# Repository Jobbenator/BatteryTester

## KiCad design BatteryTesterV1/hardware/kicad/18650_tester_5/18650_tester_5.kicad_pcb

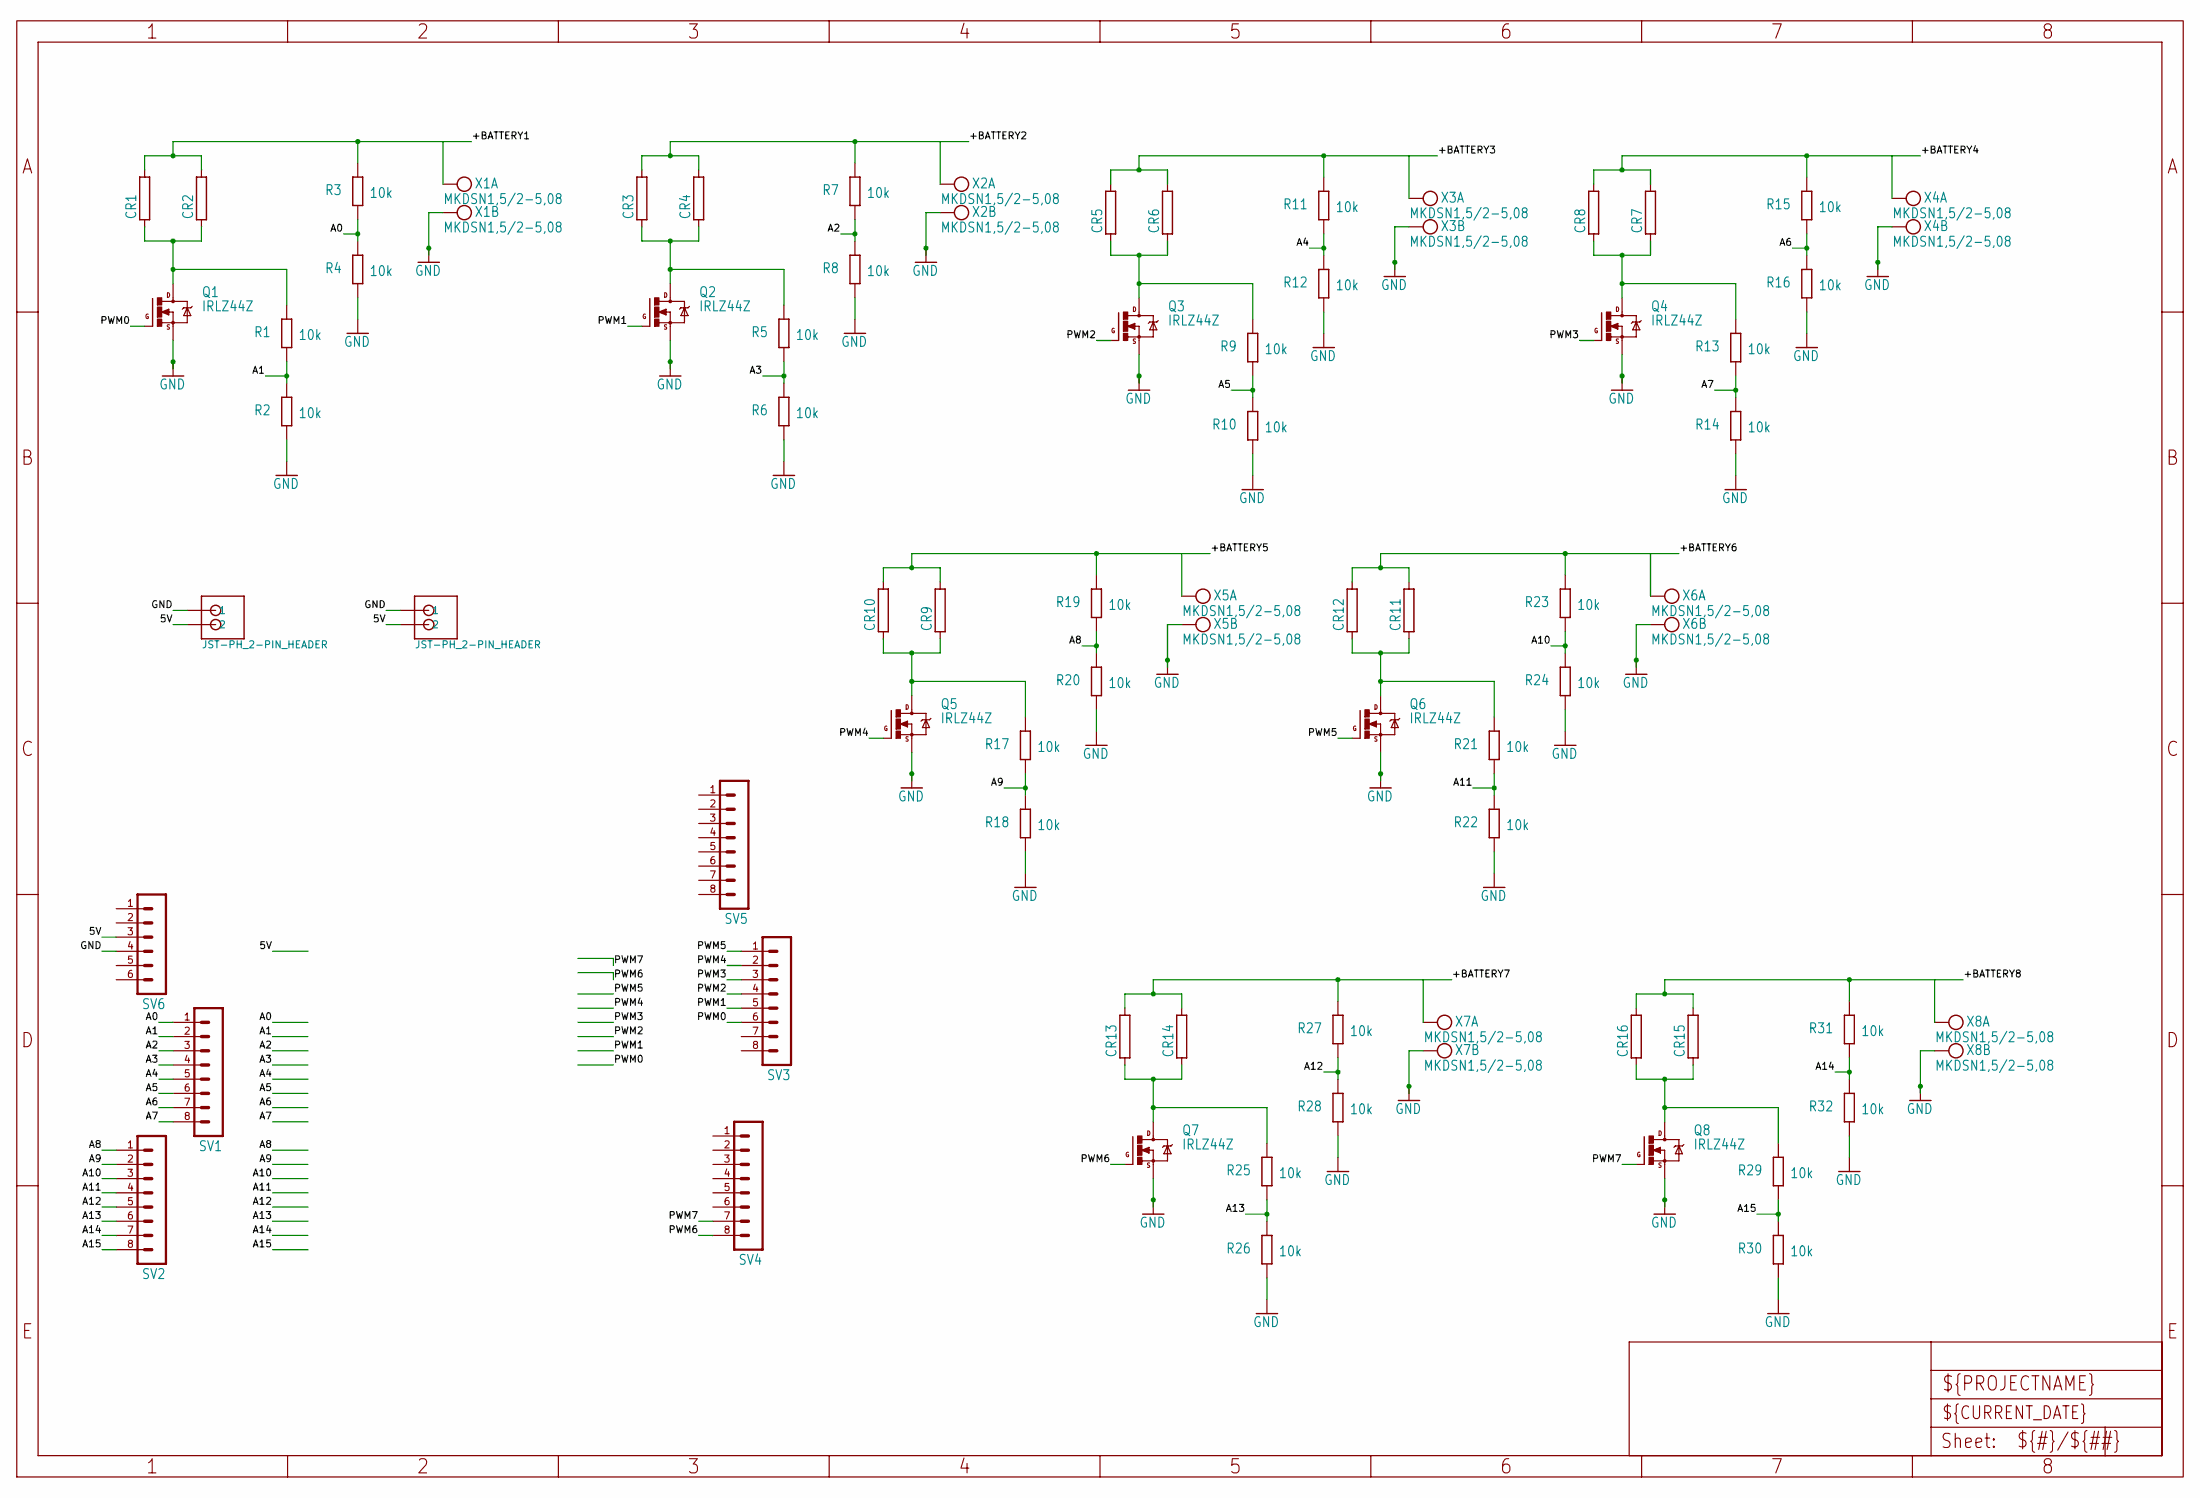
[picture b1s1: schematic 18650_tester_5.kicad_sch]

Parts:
CR1, CR2, CR3, CR4, CR5, CR6, CR7, CR8, CR9, CR10, CR11, CR12, CR13, CR14, CR15, CR16: RRWM6X22; RWM6X22
Q1, Q2, Q3, Q4, Q5, Q6, Q7, Q8: IRLZ44Z; TO220BH
R1, R2, R3, R4, R5, R6, R7, R8, R9, R10, R11, R12, R13, R14, R15, R16, R17, R18, R19, R20, R21, R22, R23, R24, R25, R26, R27, R28, R29, R30, R31, R32: 10k; M1206
SV1, SV2, SV3, SV4, SV5: MA08-1
SV6: MA06-1
U$2, U$3: JST-PH_2-PIN_HEADER; JST_B2B-PH_HEADER
X1, X2, X3, X4, X5, X6, X7, X8: MKDSN1,5/2-5,08; MKDSN1,5_2-5,08

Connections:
5V: SV6.3, U$2.P2 (2), U$3.P2 (2)
+BATTERY1: CR1.2, CR2.2, R3.2, X1.1
+BATTERY2: CR3.2, CR4.2, R7.2, X2.1
+BATTERY3: CR5.2, CR6.2, R11.2, X3.1
+BATTERY4: CR7.2, CR8.2, R15.2, X4.1
+BATTERY5: CR9.2, CR10.2, R19.2, X5.1
+BATTERY6: CR11.2, CR12.2, R23.2, X6.1
+BATTERY7: CR13.2, CR14.2, R27.2, X7.1
+BATTERY8: CR15.2, CR16.2, R31.2, X8.1
A0: R3.1, R4.2, SV1.1
A1: R1.1, R2.2, SV1.2
A2: R7.1, R8.2, SV1.3
A3: R5.1, R6.2, SV1.4
A4: R11.1, R12.2, SV1.5
A5: R9.1, R10.2, SV1.6
A6: R15.1, R16.2, SV1.7
A7: R13.1, R14.2, SV1.8
A8: R19.1, R20.2, SV2.1
A9: R17.1, R18.2, SV2.2
A10: R23.1, R24.2, SV2.3
A11: R21.1, R22.2, SV2.4
A12: R27.1, R28.2, SV2.5
A13: R25.1, R26.2, SV2.6
A14: R31.1, R32.2, SV2.7
A15: R29.1, R30.2, SV2.8
GND: Q1.S, Q2.S, Q3.S, Q4.S, Q5.S, Q6.S, Q7.S, Q8.S, R2.1, R4.1, R6.1, R8.1, R10.1, R12.1, R14.1, R16.1, R18.1, R20.1, R22.1, R24.1, R26.1, R28.1, R30.1, R32.1, SV6.4, U$2.P1 (1), U$3.P1 (1), X1.2, X2.2, X3.2, X4.2, X5.2, X6.2, X7.2, X8.2
unnamed: CR3.1, CR4.1, Q2.D, R5.2
unnamed: CR5.1, CR6.1, Q3.D, R9.2
unnamed: CR1.1, CR2.1, Q1.D, R1.2
unnamed: CR7.1, CR8.1, Q4.D, R13.2
unnamed: CR9.1, CR10.1, Q5.D, R17.2
unnamed: CR11.1, CR12.1, Q6.D, R21.2
unnamed: CR13.1, CR14.1, Q7.D, R25.2
unnamed: CR15.1, CR16.1, Q8.D, R29.2
PWM0: Q1.G, SV3.6
PWM1: Q2.G, SV3.5
PWM2: Q3.G, SV3.4
PWM3: Q4.G, SV3.3
PWM4: Q5.G, SV3.2
PWM5: Q6.G, SV3.1
PWM6: Q7.G, SV4.8
PWM7: Q8.G, SV4.7

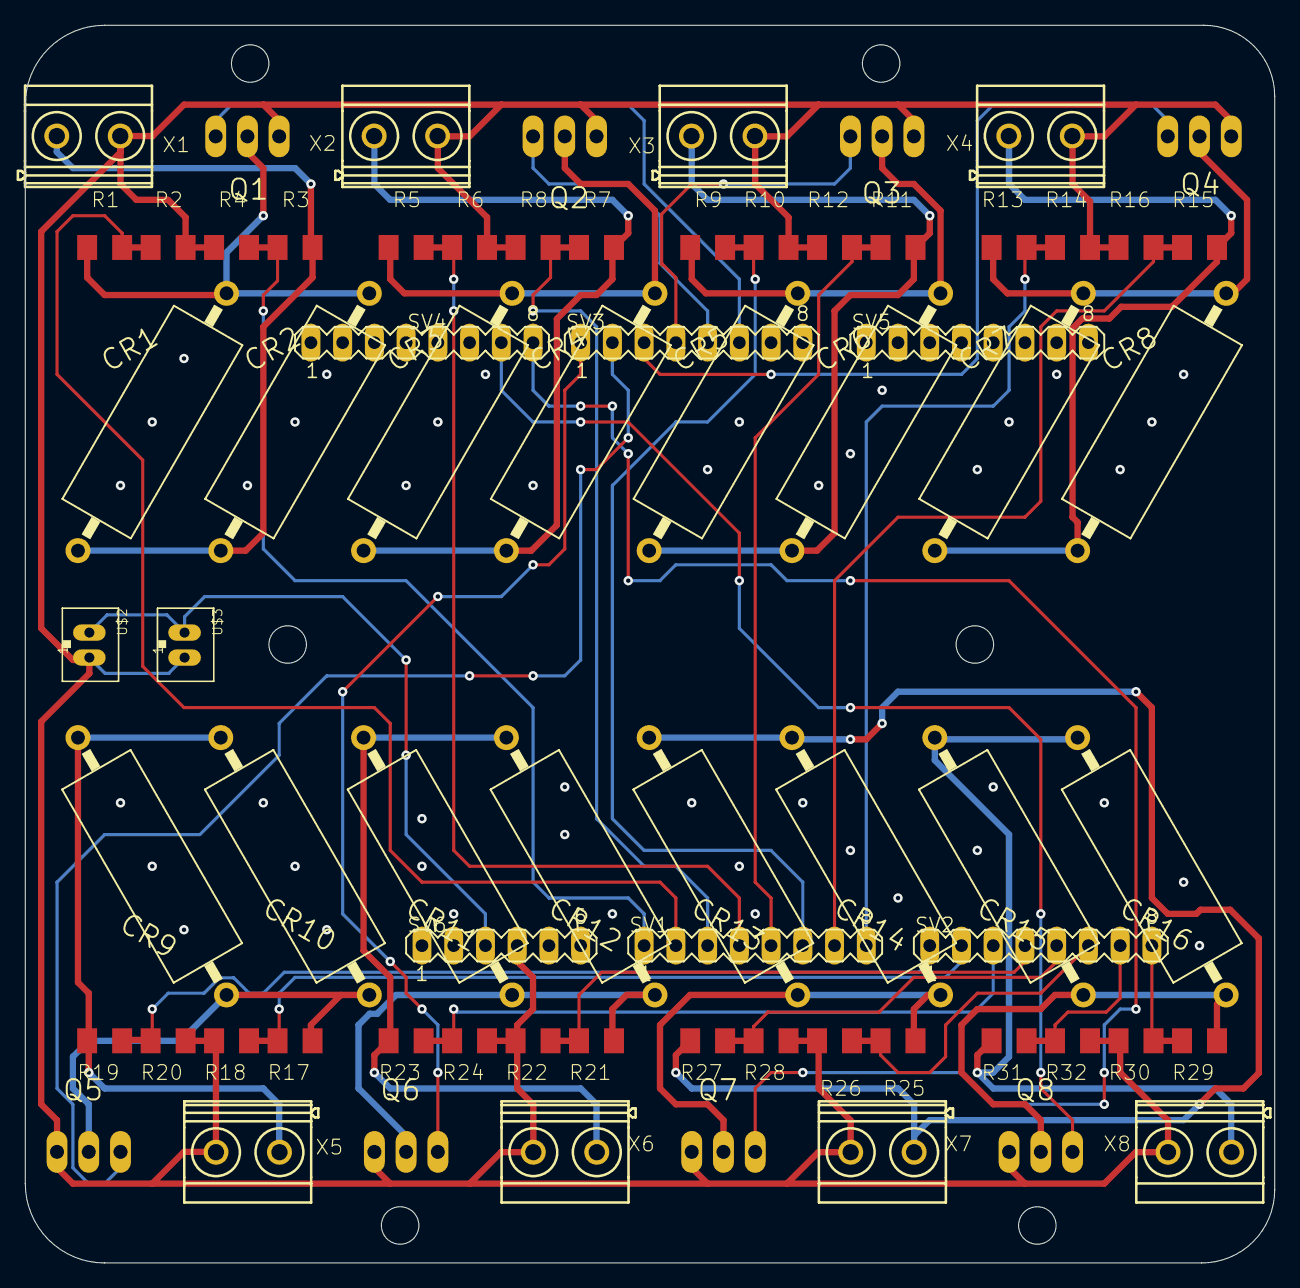
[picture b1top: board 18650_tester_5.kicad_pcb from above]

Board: 2 copper layers, 100.0 x 99.1 mm, 78 parts (0 on the bottom side), 42 nets.

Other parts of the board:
@HOLE0, @HOLE1, @HOLE2, @HOLE3, @HOLE4, @HOLE5: (no value)

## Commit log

2023-07-01 some folders added and a readme
2023-07-10 Readme updated and arduino file fix
2023-07-18 More files added.
